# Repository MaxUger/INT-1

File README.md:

# INT-1
 Mechanical Keypad.
 
 Backside:

 Frontside:

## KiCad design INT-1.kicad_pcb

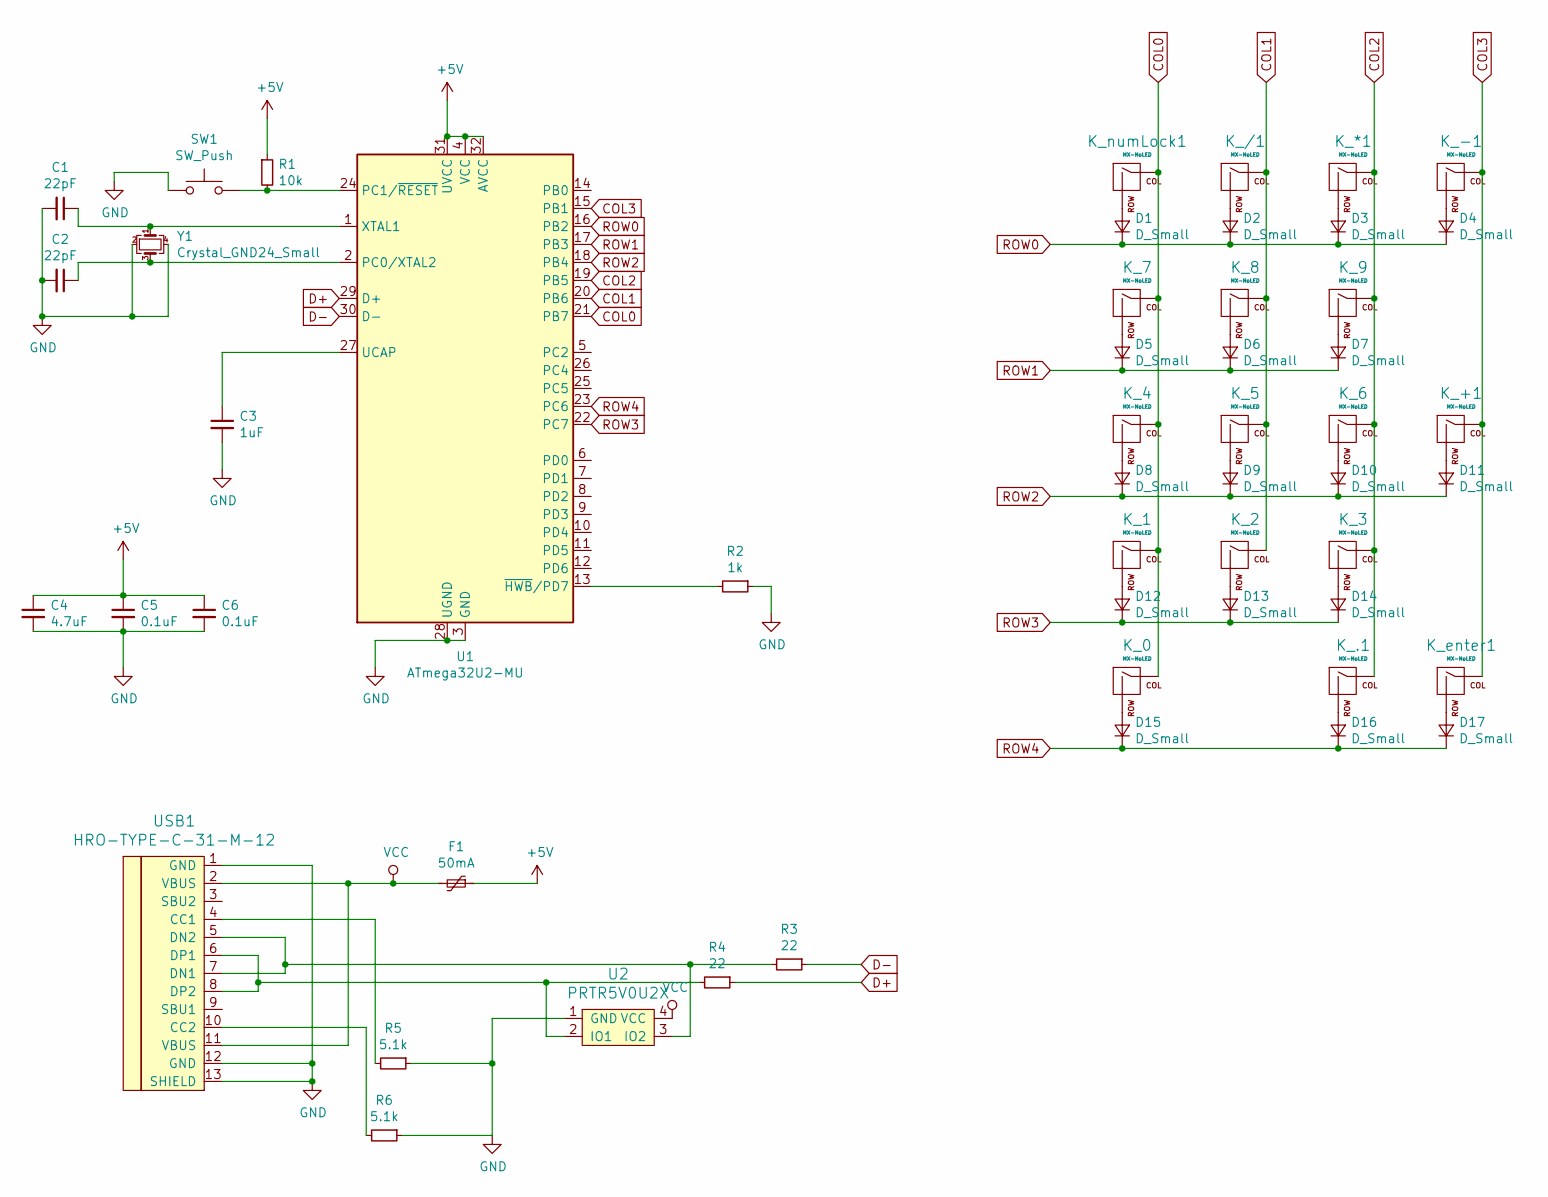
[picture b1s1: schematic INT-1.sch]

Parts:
C1, C2: 22pF; C_0603_1608Metric
C3: 1uF; C_0603_1608Metric
C4: 4.7uF; C_0603_1608Metric
C5, C6: 0.1uF; C_0603_1608Metric
D1, D2, D3, D4, D5, D6, D7, D8, D9, D10, D11, D12, D13, D14, D15, D16, D17: D_Small; D_SOD-123
F1: 50mA; Fuse_1206_3216Metric
K_0: MX-NoLED; MXOnly-2U-Hotswap
K_1, K_2, K_3, K_4, K_5, K_6, K_7, K_8, K_9, K_.1: MX-NoLED; MXOnly-1U-Hotswap
K_*1: MX-NoLED; MXOnly-1U-Hotswap
K_+1: MX-NoLED; MX-2U-Hotswap-Vertical
K_-1: MX-NoLED; MXOnly-1U-Hotswap
K_/1: MX-NoLED; MXOnly-1U-Hotswap
K_enter1: MX-NoLED; MX-2U-Hotswap-Vertical
K_numLock1: MX-NoLED; MXOnly-1U-Hotswap
R1: 10k; R_0805_2012Metric
R2: 1k; R_0805_2012Metric
R3, R4: 22; R_0805_2012Metric
R5, R6: 5.1k; R_0805_2012Metric
SW1: SW_Push; SKQG-1155865
U1: ATmega32U2-MU; QFN-32-1EP_5x5mm_P0.5mm_EP3.1x3.1mm
U2: PRTR5V0U2X; SOT143B
USB1: HRO-TYPE-C-31-M-12
Y1: Crystal_GND24_Small; Crystal_SMD_3225-4Pin_3.2x2.5mm

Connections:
+5V: C4.1, C5.1, C6.1, F1.1, R1.1, U1.4 (VCC), U1.31 (UVCC), U1.32 (AVCC)
COL0: K_0.1 (COL), K_1.1 (COL), K_4.1 (COL), K_7.1 (COL), K_numLock1.1 (COL), U1.21 (PB7)
COL1: K_2.1 (COL), K_5.1 (COL), K_8.1 (COL), K_/1.1 (COL), U1.20 (PB6)
COL2: K_3.1 (COL), K_6.1 (COL), K_9.1 (COL), K_*1.1 (COL), K_.1.1 (COL), U1.19 (PB5)
COL3: K_+1.1 (COL), K_-1.1 (COL), K_enter1.1 (COL), U1.15 (PB1)
D+: R4.1, U1.29 (D+)
D-: R3.1, U1.30 (D-)
GND: C1.2, C2.2, C3.2, C4.2, C5.2, C6.2, R2.1, R5.1, R6.1, SW1.1, U1.3 (GND), U1.28 (UGND), U1.33 (GND), U2.1 (GND), USB1.1 (GND), USB1.12 (GND), USB1.13 (SHIELD), Y1.2, Y1.4
unnamed: C1.1, U1.1 (XTAL1), Y1.1
unnamed: C2.1, U1.2 (PC0/XTAL2), Y1.3
unnamed: C3.1, U1.27 (UCAP)
unnamed: D1.2 (A), K_numLock1.2 (ROW)
unnamed: D2.2 (A), K_/1.2 (ROW)
unnamed: D3.2 (A), K_*1.2 (ROW)
unnamed: D4.2 (A), K_-1.2 (ROW)
unnamed: D5.2 (A), K_7.2 (ROW)
unnamed: D6.2 (A), K_8.2 (ROW)
unnamed: D7.2 (A), K_9.2 (ROW)
unnamed: D8.2 (A), K_4.2 (ROW)
unnamed: D9.2 (A), K_5.2 (ROW)
unnamed: D10.2 (A), K_6.2 (ROW)
unnamed: D11.2 (A), K_+1.2 (ROW)
unnamed: D12.2 (A), K_1.2 (ROW)
unnamed: D13.2 (A), K_2.2 (ROW)
unnamed: D14.2 (A), K_3.2 (ROW)
unnamed: D15.2 (A), K_0.2 (ROW)
unnamed: D16.2 (A), K_.1.2 (ROW)
unnamed: D17.2 (A), K_enter1.2 (ROW)
unnamed: R1.2, SW1.2, U1.24 (PC1/~RESET)
unnamed: R2.2, U1.13 (~HWB~/PD7)
unnamed: R3.2, U2.3 (IO2), USB1.5 (DN2), USB1.7 (DN1)
unnamed: R4.2, U2.2 (IO1), USB1.6 (DP1), USB1.8 (DP2)
unnamed: R5.2, USB1.4 (CC1)
unnamed: R6.2, USB1.10 (CC2)
ROW0: D1.1 (K), D2.1 (K), D3.1 (K), D4.1 (K), U1.16 (PB2)
ROW1: D5.1 (K), D6.1 (K), D7.1 (K), U1.17 (PB3)
ROW2: D8.1 (K), D9.1 (K), D10.1 (K), D11.1 (K), U1.18 (PB4)
ROW3: D12.1 (K), D13.1 (K), D14.1 (K), U1.22 (PC7)
ROW4: D15.1 (K), D16.1 (K), D17.1 (K), U1.23 (PC6)
VCC: F1.2, U2.4 (VCC), USB1.2 (VBUS), USB1.11 (VBUS)

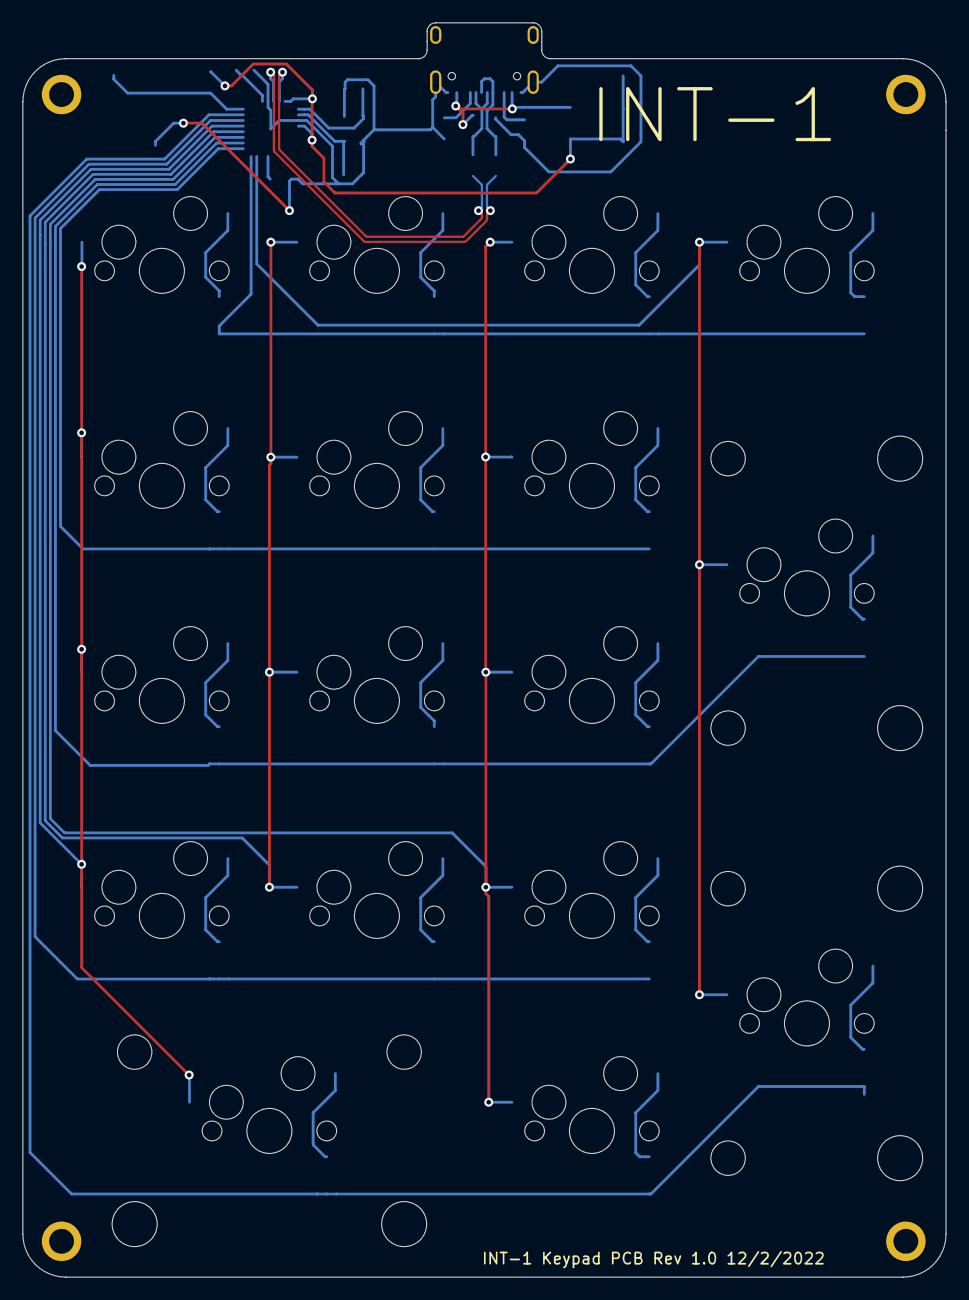
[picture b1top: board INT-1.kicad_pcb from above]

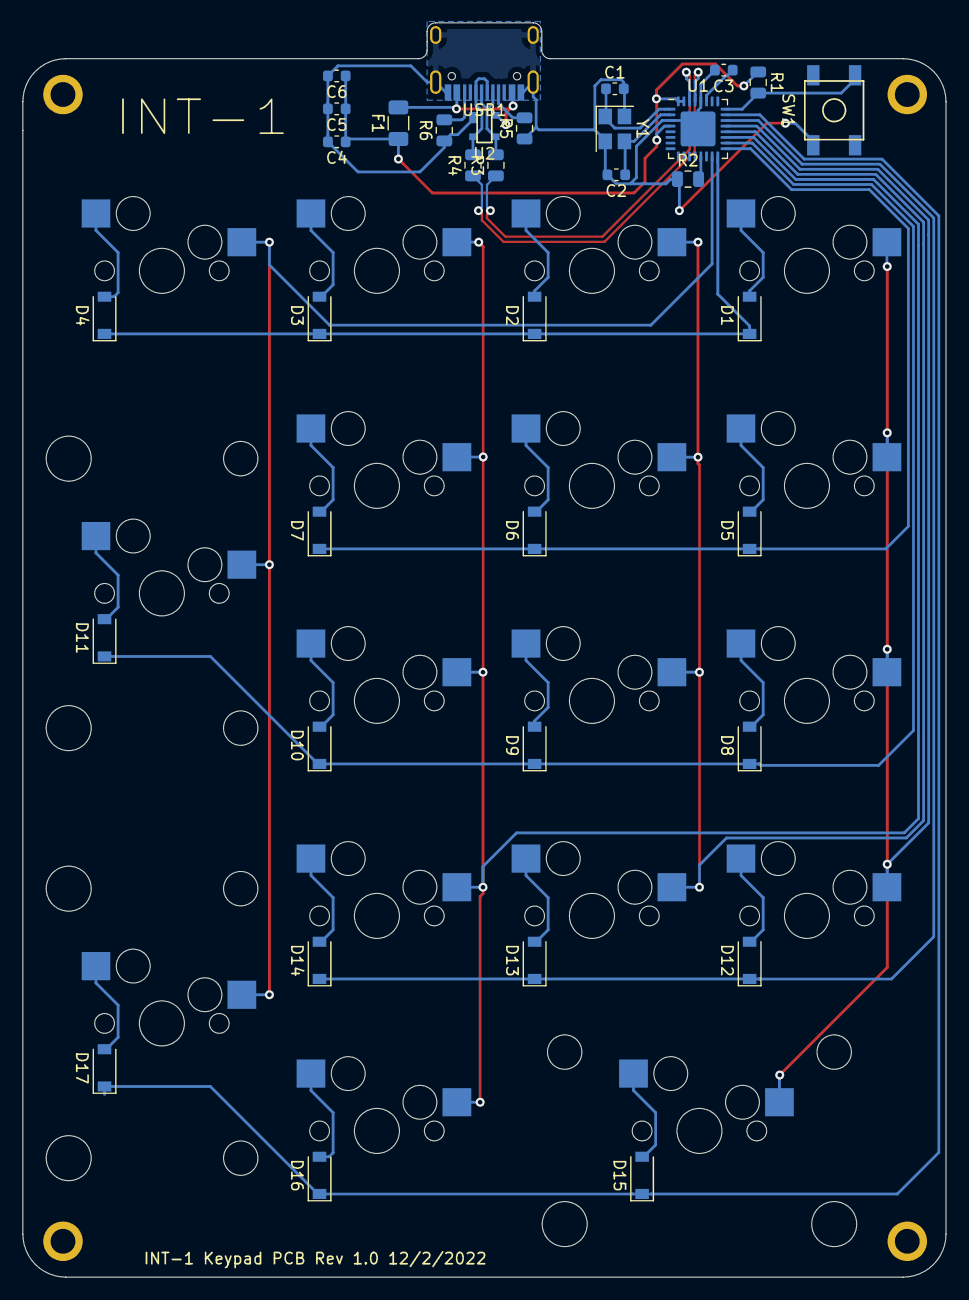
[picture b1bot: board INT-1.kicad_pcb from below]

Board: 2 copper layers, 81.8 x 111.1 mm, 52 parts (35 on the bottom side), 40 nets.

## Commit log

2022-02-08 Added Submodules
2022-02-09 Finished Schematic
2022-02-11 Assigned Footprints
2022-02-12 Finished diode placement
2022-02-12 Finished edge cuts
2022-02-13 Finished trace routing
2022-02-13 Added mounting holes
2022-02-13 Added Text
2022-02-14 Generated gerbers
2022-03-14 Added 3d models
